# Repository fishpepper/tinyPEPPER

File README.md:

# tinyPEPPER -- a tiny and lightweight 4in1 BLHeli_S ESC

My approach to build a small and lightweight ESC.

See [http://fishpepper.de/projects/tinyPEPPER](http://fishpepper.de/projects/tinyPEPPER) for more details.

This thing is TINY! The outer dimensions are 20x20mm with a 16mm hole-to-hole spacing.
It runs BLHELI_S 

Key features:
- 16x16mm hole-to-hole spacing
- 1.2g (!)
- BLHeli_S with DSHOT300
- 1S only (really!)

This work is published under the CERN open hardware license v1.2. 
Feel free to use the design - but make sure to give proper credit 
and release all modifications under the same license! 
See LICENSE.txt for details!

THIS COMES WITH NO WARRANTY! BUILD, FLY, AND USE AT YOUR OWN RISK!

# Build your own

Make sure to init the git submodule for the libraries in the
kicad_misc directory by calling git submodule init && git submodule update.
You will have to use a recent kicad version, i used the commit #efdfaeb
when i designed this circuit board. Older versions will probably not work.

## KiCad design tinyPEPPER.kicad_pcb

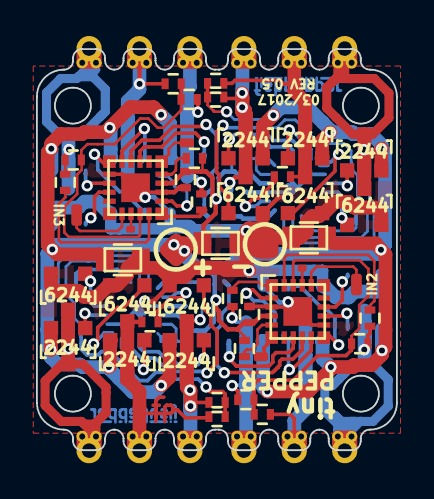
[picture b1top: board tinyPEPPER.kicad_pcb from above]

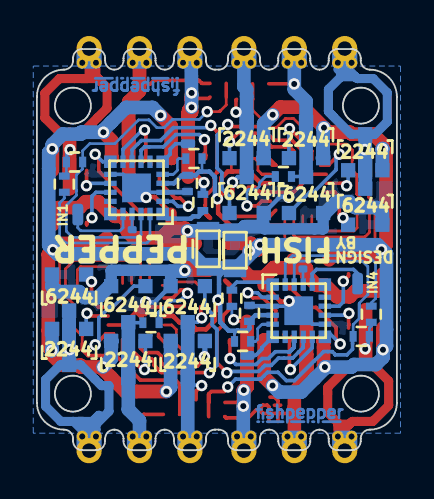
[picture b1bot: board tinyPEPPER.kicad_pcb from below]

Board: 2 copper layers, 20.0 x 22.3 mm, 97 parts (48 on the bottom side), 70 nets.

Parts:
BL_TX1, BL_TX2, BL_TX3, BL_TX4: TP; TP_smd_0.5x0.4
C201, C301, C401, C501, C1000: 47u; C_0805
C202, C302, C402, C502: 100n; C_0402_CUSTOM
FET201, FET203, FET205, FET301, FET303, FET305, FET401, FET403, FET405, FET501, FET503, FET505: IRLML6244; SOT-23
FET202, FET204, FET206, FET302, FET304, FET306, FET402, FET404, FET406, FET502, FET504, FET506: IRLML2244; SOT-23
FISHPEPPER: Val**; fishpepper_copper
FISHPEPPER#2: Val**; fishpepper_copper
H1, H2, H3, H4: hole; mouting_hole
OUT_A201, OUT_A301, OUT_A401, OUT_A501: TP; TP_PHASE_PAD
OUT_B201, OUT_B301, OUT_B401, OUT_B501: TP; TP_PHASE_PAD
OUT_C201, OUT_C301, OUT_C401, OUT_C501: TP; TP_PHASE_PAD
R201, R202, R204, R206, R301, R302, R304, R306, R401, R402, R404, R406, R501, R502, R504, R506: 1k; R_0402_CUSTOM
R203, R205, R207, R303, R305, R307, R403, R405, R407, R503, R505, R507: 10k; R_0402_CUSTOM
TP101, TP102: TP; TP_powerpad
TP103, TP104, TP105, TP106: TP; tp_SMD_0.6x1.2
TP202, TP302, TP402, TP502: TP; TP_smd_0.5x0.8
U201, U301, U401, U501: EFM8BB21; QFN20

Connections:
/RC_IN_0: TP103.1, U201.17
/RC_IN_1: TP104.1, U301.17
/single esc 1/Ac_0: FET202.1, U201.13
/single esc 1/Ap_0: FET201.1, U201.14
/single esc 1/Bc_0: FET204.1, U201.10
/single esc 1/Bp_0: FET203.1, U201.11
/single esc 1/C2D_0: TP202.1, U201.6
/single esc 1/Cc_0: FET206.1, U201.8
/single esc 1/Cp_0: FET205.1, U201.9
/single esc 1/PHASE_A_0: FET201.3, FET202.3, OUT_A201.1, R202.2, R203.1
/single esc 1/PHASE_B_0: FET203.3, FET204.3, OUT_B201.1, R204.2, R205.1
/single esc 1/PHASE_C_0: FET205.3, FET206.3, OUT_C201.1, R206.2, R207.1
/single esc 2/Ac_0: FET302.1, U301.13
/single esc 2/Ap_0: FET301.1, U301.14
/single esc 2/Bc_0: FET304.1, U301.10
/single esc 2/Bp_0: FET303.1, U301.11
/single esc 2/C2D_0: TP302.1, U301.6
/single esc 2/Cc_0: FET306.1, U301.8
/single esc 2/Cp_0: FET305.1, U301.9
/single esc 2/PHASE_A_0: FET301.3, FET302.3, OUT_A301.1, R302.2, R303.1
/single esc 2/PHASE_B_0: FET303.3, FET304.3, OUT_B301.1, R304.2, R305.1
/single esc 2/PHASE_C_0: FET305.3, FET306.3, OUT_C301.1, R306.2, R307.1
/single esc 3/Ac_0: FET402.1, U401.13
/single esc 3/Ap_0: FET401.1, U401.14
/single esc 3/Bc_0: FET404.1, U401.10
/single esc 3/Bp_0: FET403.1, U401.11
/single esc 3/C2D_0: TP402.1, U401.6
/single esc 3/Cc_0: FET406.1, U401.8
/single esc 3/Cp_0: FET405.1, U401.9
/single esc 3/PHASE_A_0: FET401.3, FET402.3, OUT_A401.1, R402.2, R403.1
/single esc 3/PHASE_B_0: FET403.3, FET404.3, OUT_B401.1, R404.2, R405.1
/single esc 3/PHASE_C_0: FET405.3, FET406.3, OUT_C401.1, R406.2, R407.1
/single esc 3/RC_IN: TP105.1, U401.17
/single esc 4/Ac_0: FET502.1, U501.13
/single esc 4/Ap_0: FET501.1, U501.14
/single esc 4/Bc_0: FET504.1, U501.10
/single esc 4/Bp_0: FET503.1, U501.11
/single esc 4/C2D_0: TP502.1, U501.6
/single esc 4/Cc_0: FET506.1, U501.8
/single esc 4/Cp_0: FET505.1, U501.9
/single esc 4/PHASE_A_0: FET501.3, FET502.3, OUT_A501.1, R502.2, R503.1
/single esc 4/PHASE_B_0: FET503.3, FET504.3, OUT_B501.1, R504.2, R505.1
/single esc 4/PHASE_C_0: FET505.3, FET506.3, OUT_C501.1, R506.2, R507.1
/single esc 4/RC_IN: TP106.1, U501.17
GND: C201.1, C202.1, C301.1, C302.1, C401.1, C402.1, C501.1, C502.1, C1000.1, FET201.2, FET203.2, FET205.2, FET301.2, FET303.2, FET305.2, FET401.2, FET403.2, FET405.2, FET501.2, FET503.2, FET505.2, TP102.1, U201.3, U201.12, U201.21, U301.3, U301.12, U301.21, U401.3, U401.12, U401.21, U501.3, U501.12, U501.21
unnamed: BL_TX1.1, U201.18
unnamed: BL_TX2.1, U301.18
unnamed: BL_TX3.1, U401.18
unnamed: BL_TX4.1, U501.18
unnamed: R201.1, U201.5
unnamed: R202.1, R204.1, R206.1, U201.19
unnamed: R203.2, U201.20
unnamed: R205.2, U201.2
unnamed: R207.2, U201.1
unnamed: R301.1, U301.5
unnamed: R302.1, R304.1, R306.1, U301.19
unnamed: R303.2, U301.20
unnamed: R305.2, U301.2
unnamed: R307.2, U301.1
unnamed: R401.1, U401.5
unnamed: R402.1, R404.1, R406.1, U401.19
unnamed: R403.2, U401.20
unnamed: R405.2, U401.2
unnamed: R407.2, U401.1
unnamed: R501.1, U501.5
unnamed: R502.1, R504.1, R506.1, U501.19
unnamed: R503.2, U501.20
unnamed: R505.2, U501.2
unnamed: R507.2, U501.1
VCC: C201.2, C202.2, C301.2, C302.2, C401.2, C402.2, C501.2, C502.2, C1000.2, FET202.2, FET204.2, FET206.2, FET302.2, FET304.2, FET306.2, FET402.2, FET404.2, FET406.2, FET502.2, FET504.2, FET506.2, R201.2, R301.2, R401.2, R501.2, TP101.1, U201.4, U301.4, U401.4, U501.4

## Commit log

2017-02-15 added submodule
2017-02-15 fixed image
2017-02-21 cleanup to custom parts
2017-02-21 added lib
2017-02-21 phase tabs
2017-02-21 added graphics
2017-02-21 fixed docs
2017-03-23 new motor tabs and switched to efm8bb21 (same pad layout)
2017-03-23 added doc
